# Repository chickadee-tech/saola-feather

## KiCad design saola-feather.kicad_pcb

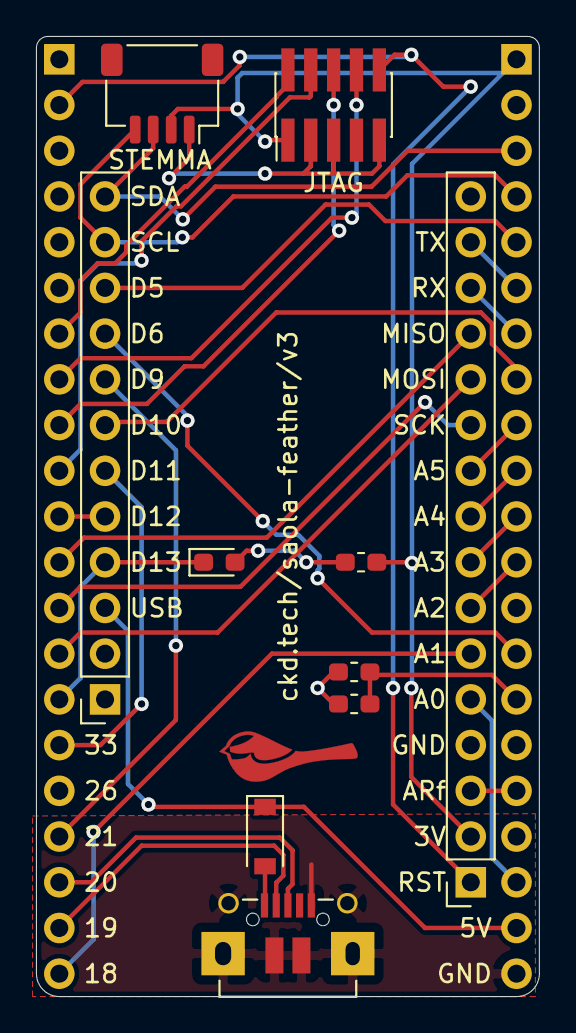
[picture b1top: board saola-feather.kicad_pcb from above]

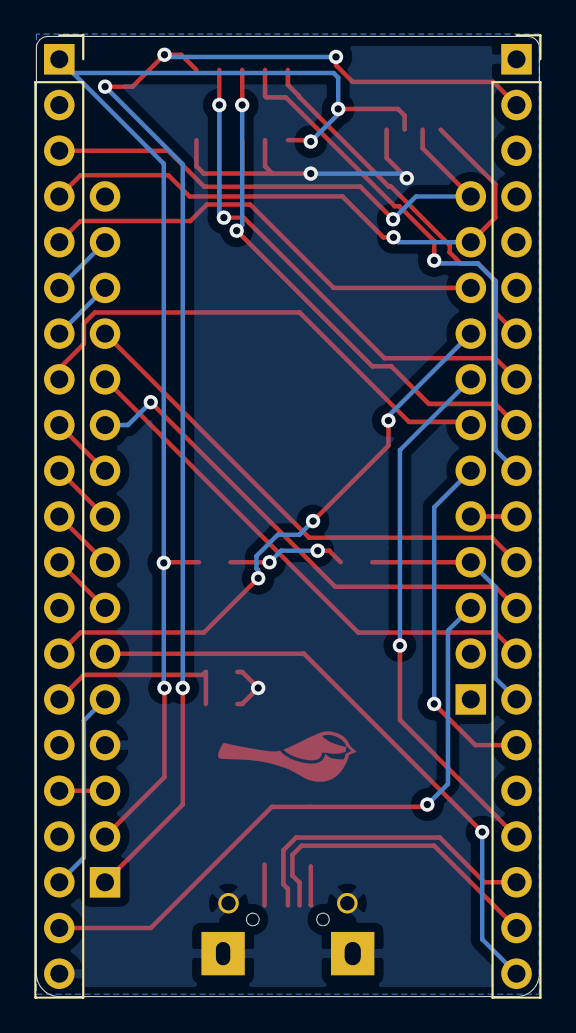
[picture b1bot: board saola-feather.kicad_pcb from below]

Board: 2 copper layers, 27.9 x 53.3 mm, 12 parts (2 on the bottom side), 34 nets.

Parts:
C1: 1uF; C_0603_1608Metric_Pad1.05x0.95mm_HandSolder
D1: D_Small; D_SOD-123
D2: LED_Small; LED_0603_1608Metric_Pad1.05x0.95mm_HandSolder
J1, J7: Conn_01x21_Female; PinSocket_1x21_P2.54mm_Vertical
J2: FeatherTop; PinSocket_1x12_P2.54mm_Vertical
J3: Conn_01x04_Male; JST_SH_SM04B-SRSS-TB_1x04-1MP_P1.00mm_Horizontal
J4: USB_B_Micro; 4UCONN_20329_V2_USB
J5: FeatherBottom; PinSocket_1x16_P2.54mm_Vertical
J6: Conn_02x05_Odd_Even; PinHeader_2x05_P1.27mm_Vertical_SMD
R1: R_Small; R_0603_1608Metric_Pad1.05x0.95mm_HandSolder
R2: 100k+; R_0603_1608Metric_Pad1.05x0.95mm_HandSolder

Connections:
+3V3: J1.1, J3.2, J5.2, J6.1, R1.1
+5V: D1.1, J1.20, J2.3
/IO1: J1.3, J2.12, J3.3
/IO2: J1.4, J2.11, J3.4
/IO3: J1.5, J2.10
/IO4: J1.6, J5.15
/IO5: J1.7, J5.14
/IO6: J1.8, J2.7
/IO7: J1.9, J5.10
/IO8: J1.10, J5.9
/IO9: J1.11, J5.8
/IO10: J1.12, J5.7
/IO12: J1.14, J2.9
/IO13: C1.1, J1.15, R2.1
/IO15: J1.17, J5.3
/IO17: J1.19, J5.5
/IO18: J5.6, J7.21
/IO21: J2.8, J7.18
/IO33: J2.6, J7.16
/IO34: D2.1, J2.4, J7.15
/IO35: J5.12, J7.14
/IO36: J5.11, J7.13
/IO37: J5.13, J7.12
/IO38: J2.5, J7.11
/RST: J5.1, J6.10, J7.2
/TCK_IO39: J6.4, J7.10
/TDI_IO41: J6.8, J7.8
/TDO_IO40: J6.6, J7.9
/TMS_IO42: J6.2, J7.7
/USB+: J4.3, J7.19
/USB-: J4.2, J7.20
GND: C1.2, J1.21, J3.1, J4.5, J4.6, J5.4, J6.3, J6.5, J6.9, J7.1, R2.2
unnamed: D1.2, J4.1
unnamed: D2.2, R1.2

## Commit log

2020-05-24 First revision
2020-06-09 Second version with fixed I2C
2020-07-24 Add RC circuit for reset. V3
2020-07-24 Tweak pinout:
    * D10 is now IO6
    * A5 is IO7
    * A4 is IO8
    * A3 is IO9
    * A2 is IO10
